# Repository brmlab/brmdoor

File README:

=== Brmdoor control software ===

brmd/ - integration hub that collects data from various sources and provides
unified reporting on IRC and web etc.
install dependecies:
  aptitude install git libimage-magick-perl liblogger-syslog-perl libdevice-serialport-perl\
    libpoe-perl libtie-ixhash-perl screen libpoe-component-server-http-perl libexpat1-dev\
    libxml-simple-perl libpoe-component-irc-perl arduino-mk
  cpan> install WWW::WolframAlpha

brmdoor/ - Arduino software

Project webpage: http://brmlab.cz/project/brmdoor

Note for PN532 version: if you want brmdoor to add card UID after "CARD"
message (not just nick), set printFullUID to true in brmdoor/brmdoor.ino.

==== Adding new UIDs to the database ====

There are two lists - the new proper and the old deperecated with truncated UIDs.
When adding, the new list is better place.

The new proper list is searched for UIDs first.

===== Using the new proper list - recommended =====

Edit the cardids_proper.h file and add your UID and nick to a new line, which
will become part of the ACLproper array. E.g. to add UID 04c24ce9ad2780 that is
7 bytes long and adding nick "voyeur1", add line:

  { 7, {0x04, 0xc2  0x4c, 0xe9, 0xad, 0x27, 0x80}, "voyeur1" },

===== Using the old broken truncated list - not recommended =====

Edit the cardids.h file. If the new card UID is 4 bytes long, e.g. 35b018d4,
compute BCC, which is xor of these four bytes (0x49 in this case). Then add

  { {0x00, 0x00, 0x35, 0xb0, 0x18, 0xd4, 0x49}, "mifare_classic_1" },

The first two bytes are magic bytes that originate in the old reader, just use
two zero bytes as above. The last byte is BCC we computed before. But you can
use zero, the software doesn't need it.

If the card UID is longer than 4 bytes (7 or 10 bytes), e.g. 04c24ce9ad2780,
discard last four bytes of the UID and prepend 0x88. Use this "newly" created
UID as if the card had only 4 byte UID, just like above.

  { {0x00, 0x00, 0x88, 0x04, 0xc2, 0x4c, 0x02}, "truncated_voyeur1" },

The old reader didn't support ISO14443 SELECT cascade 2 and 3. Hence the broken
UIDs.

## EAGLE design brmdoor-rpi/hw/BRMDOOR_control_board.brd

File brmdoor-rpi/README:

This is quick and dirty version of brmdoor that does not require Arduino, and runs only on Raspberry Pi.

This version of brmdoor requires:
- create user brmdoor, ~brmdoor/.screenrc
- create /etc/systemd/system/brmdoor.service in case systemd is used to autostart brmdoor service
- irssi configured according to ./irssi/config with loaded scripts from ./irssi/scripts
- libnfc-compatible smartcard reader
- libnfc installed
- create /etc/nfc/libnfc.conf using content from libnfc.conf supplied (otherwise nfc-list wouldnt find your NFC device)
- nfc-getcard.c compiled against libnfc (with -lnfc) and saved as "./nfc-getcard"
- to be running on RaspberryPi (or simillar with GPIO pins exported through /proc)
- variables in brmdoor-rpi.sh modified according to reality
- list of allowed cards in allowed.list in the correct format

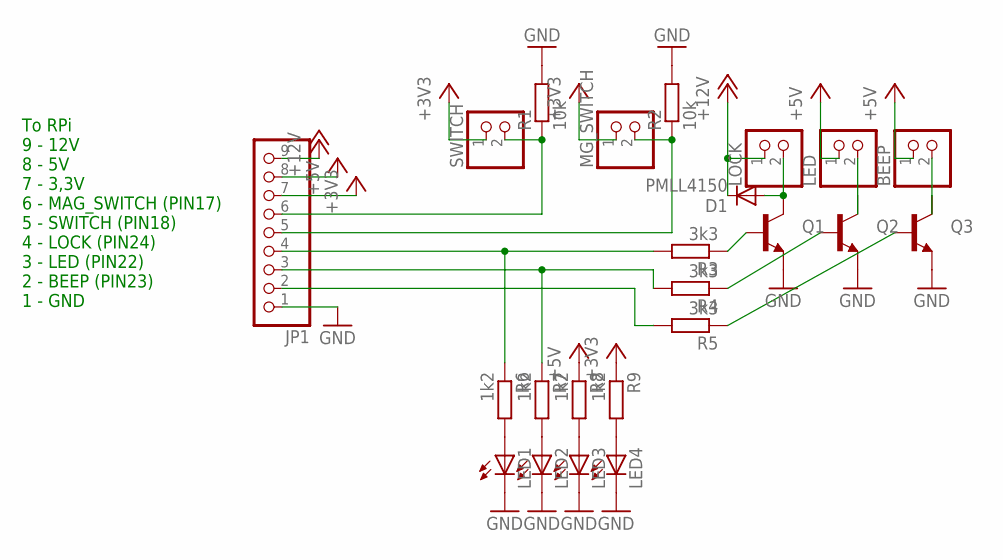
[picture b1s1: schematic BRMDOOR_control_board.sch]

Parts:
BEEP: PINHD-1X2; 1X02
D1: PMLL4150; SOD80C
JP1: PINHD-1X9; 1X09
LED: PINHD-1X2; 1X02
LED1, LED2, LED3, LED4: LEDKA-3528ASYC; KA-3528ASYC
LOCK: PINHD-1X2; 1X02
MG_SWITCH: PINHD-1X2; 1X02
Q1, Q2, Q3: TRANSISTOR_NPNSMD2; SOT223
R1, R2: 10k; M1206
R3, R4, R5: 3k3; M1206
R6, R7, R8, R9: 1k2; M1206
SWITCH: PINHD-1X2; 1X02

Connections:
+3V3: JP1.7, MG_SWITCH.1, R9.1, SWITCH.1
+5V: BEEP.1, JP1.8, LED.1, R8.1
+12V: D1.C, JP1.9, LOCK.1
GND: JP1.1, LED1.C, LED2.C, LED3.C, LED4.C, Q1.3 (E), Q2.3 (E), Q3.3 (E), R1.2, R2.2
unnamed: JP1.6, R1.1, SWITCH.2
unnamed: JP1.5, MG_SWITCH.2, R2.1
unnamed: Q1.1 (B), R3.1
unnamed: Q2.1 (B), R4.1
unnamed: Q3.1 (B), R5.1
unnamed: JP1.4, R3.2, R6.1
unnamed: JP1.3, R4.2, R7.1
unnamed: JP1.2, R5.2
unnamed: LED1.A, R6.2
unnamed: LED2.A, R7.2
unnamed: LED3.A, R8.2
unnamed: LED4.A, R9.2
unnamed: D1.A, LOCK.2, Q1.2 (C)
unnamed: LED.2, Q2.2 (C)
unnamed: BEEP.2, Q3.2 (C)

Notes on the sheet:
To RPi 9 - 12V 8 - 5V 7 - 3,3V 6 - MAG_SWITCH (PIN17) 5 - SWITCH (PIN18) 4 - LOCK (PIN24) 3 - LED (PIN22) 2 - BEEP (PIN23) 1 - GND

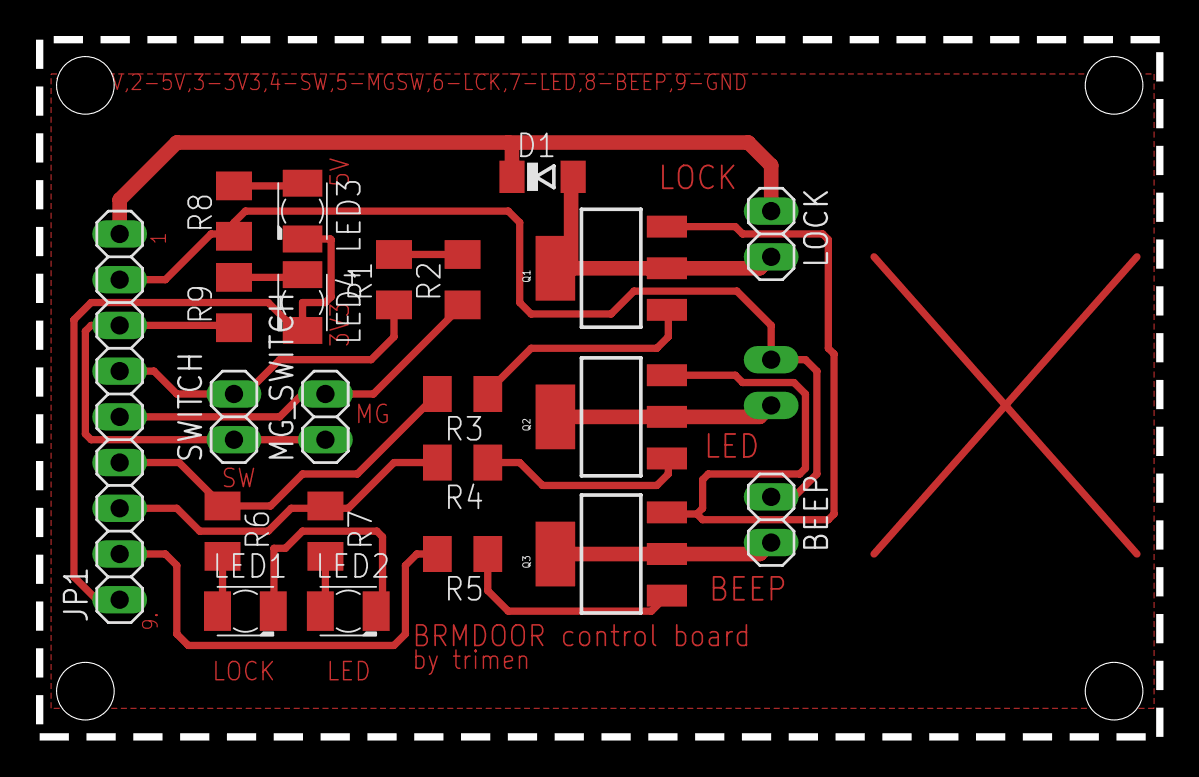
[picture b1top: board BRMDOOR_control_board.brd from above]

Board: 2 copper layers, 62.2 x 38.7 mm, 23 parts (1 on the bottom side), 19 nets.

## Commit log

2010-11-08 init
2010-11-12 started to work on C rewrite to deploy directly on WRT
2010-12-09 add WIP python version
2011-03-09 Remove unfinished experiments
2011-03-09 Replace brmdoor.php by full-fledged universal hub script brmd
    brmd should handle various kinds of brmlab-related events (brmdoor
    unlocks, status panel events, wiki updates) and provide central place
    to handle them, with unified interface (web and IRC).
    Currently, all of this should be implemented, except wiki updates
    handling. But the script is still a bit rudimentary; some TODO items
    are mentioned in the TODO file.
2011-03-09 brmstatus.txt interface support
2011-03-09 brmd.pl: Fix permissions
2011-03-09 brmstatus.txt: Add link to front page
2011-03-09 Web /brmd/: Add link to view source
2011-03-09 add arduino sketch
2011-03-09 add pitches.h
2011-03-09 use macro for music
2011-03-11 brmd: Try to deal with IRC disconnects gracefully
2011-03-11 brmdoor: Add timestamps to log, log each brmdoor input for now
2011-03-11 brmd IRC: Sync topic with internal state on connect
2011-03-13 Move files to directories brmd/, sketch/
2011-03-13 sketch: Convert from ethernet shield to USB serial comunication
    Ethernet shield has been extremely unreliable, and we need a USB host nearby for a webcam anyway.
2011-03-14 brmd: Brmdoor is no longer TCP service but local serial
2011-03-16 small fixes, add NewSoftSerial lib
2011-04-26 sketch: Support for status overrides from host over comSerial
2011-04-26 brmd: Update icons
2011-04-26 brmd: Force HTTP/1.1 replies
    It seems to reduce the fd leaks by an order of magnitude.
2011-04-26 brmd: Factor out status_update(), record_update()
2011-04-26 brmd: Support for manual status override using web button
2011-05-01 brmd.pl web_brmstatus_html: Change input button to submit
2011-05-01 brmd: Allow device filename override on commandline
2011-05-01 remove confusing sentence
2011-05-01 add readme
2011-05-03 print also url of videostream
2011-05-03 brmd: Show stream URL only on IRC
2011-05-03 brmd: Switch streaming on brmvid when record switch is pressed
2011-05-03 brmd: Show brmstream link on main web page when on air
2011-05-03 brmd: Update stream status in topic too
2011-05-03 brmd: Factor out stream URL to $streamurl
2011-05-03 brmd record_update(): Call topic_update()
2011-05-04 fix show source link
2011-05-06 brmd: Separate IRC interface to the brmd::IRC package
2011-05-06 brmd: Separate WWW interface to the brmd::WWW package
2011-05-06 brmd: Separate serial interface to the brmd::Door package
2011-05-06 brmd::WWW: Move use HTTP::Status, CGI there
2011-05-06 brmd::IRC: Replace topic_update, notify with more specific events
2011-05-06 brmd: Separate ssh interface to the brmd::Stream package
2011-05-07 brmd status_update, record_update: Transform to events, introduce event registration
2011-05-07 brmd: Move manual update logic from web_brmstatus_switch() to status_update()
2011-05-07 brmd::Door: Introduce event status_override
2011-05-07 brmd::WWW notify_update(): Merge in notify_manual_update()
2011-05-07 brmd: $record -> $streaming
2011-05-07 brmd streaming_update(): Remove superfluous line
2011-05-08 Added AlphaSign notification of streaming status
2011-05-10 brmd: Copyright notice
2011-05-10 brmd: Separate Alphasign interface to the brmd::Alphasign package
2011-05-12 brmd: $device -> $devdoor
2011-05-12 brmd::Door::register(): Fix observer refcount id
2011-05-12 TODO: Remove implemented features
2011-05-12 brmd::Alphasign: Manage serial directly, no external helper
2011-05-17 brmd: Update default device names to use by-id paths
2011-05-17 brmd: Fix taking $devasign from commandline
2011-05-17 brmd: Full support for alphasign, including all markup and web interface
2011-05-18 brmd::Alphasign: Improved input checking
2011-05-18 brmd::Alphasign: Remember last mode too
2011-05-18 brmd::Alphasign: Beep on stream_start()
2011-05-18 brmd::Alphasign: Add beep checkbox to web interface
2011-05-19 fix roll_up
2011-06-02 brmd: Update streamurl to Jenda's restreaming server
2011-06-22 add wolfram alpha (!alpha) command
2011-06-22 fix concatenation
2011-06-22 rework answer
2011-06-22 add nick
2011-06-22 use - instead of :
2011-06-22 sanitise newlines
2011-07-05 allow change of alphasign even while streaming
2011-07-05 Revert "allow change of alphasign even while streaming"
    This reverts commit adaaad8084e3b1f4ad81c1f069aa11c8cbd61aa1.
2011-07-31 fix output
2011-08-29 Enhanced WolframAlpha output display, limit number of lines
2011-08-30 brmd: Convert modes,markup from our to my, local to Alphasign
2011-08-30 Sketch: Fix reading new video/status state
2011-08-30 Fix manual status change desyncing arduino
2011-09-07 stream URL simplification
2011-09-08 few lines to README
2011-10-18 Sketch: Fix card number output
2011-10-18 Sketch: Fix override over serial
2011-10-18 brmd notify_door_unauth: Include cardid parameter
2011-10-18 brmd notify_door_*: Route through the main session
2011-10-18 brmd notify_door_unauth IRC: Bold message
2011-10-18 brmd::Log: New POE component, logging notify_door_* using Logger::Syslog
2011-10-18 IRC notify_door_unlocked: Do not log nickname due to popular demand
2011-10-18 Track dooropen ajar/shut state using a magnetic sensor, log verbosely for now
2011-10-18 Sketch: Reduce unnecessary delay after card event
2011-10-18 Sketch: Support an 'a' command to play alarm sound
2011-10-18 brmd notify_door_open: Move alert logic from IRC to main session
2011-10-18 brmd Door play_alarm: New method
2011-10-18 brmd alert: Do not trigger on door open just after brmlab closed
2011-10-19 brmd stream_switch: Use ssh username brmlab inst. of brmstream
2011-10-20 brmd::Log notify_door_open: Add logging routine
2011-10-20 brmd::IRC notify_door_open: Report only alert conditions
2011-10-20 brmd alert condition: Consider dangerous opens also in case of status manual override active
2012-02-10 brmd.pl: stopbits 2 now needed for whatever reason
2012-06-09 brmd.pl: Fix multi-channel support
2013-01-08 brmd.pl: Use HTTP/1.0 inst. of HTTP/1.1 to avoid pipelining problems (unclosed connections)
2013-01-08 brmd.pl: Disable alphasign communication in a super-dirty way
2013-01-08 brmd.pl: Add support for the SpaceAPI json output; code provided by ruza
2013-01-12 fix irc position in spaceapi json
2013-01-12 use better logo
2013-01-14 add facebook to spaceapi json
2013-02-28 spaceapi 0.13 changes prepared for future use
    validated in OpenSpaceLint validator http://openspace.slopjong.de/
    beware, can possibly break compatibility with applications with
    spaceapi 0.12 and older because "status" is string in spaceapi
    versions up to 0.12 and object in spaceapi 0.13
    http://openspace.slopjong.de/specs/0.13
    http://openspace.slopjong.de/specs/changelog
2013-05-02 end logo with .png
2013-05-02 change geocoordinates
2013-05-30 JSON formalize
2013-06-10 status -> state, cache-control
    JSON compliant to the specs 0.13, 0.12, 0.11, 0.9, 0.8 spaceapi
2013-06-11 contact.foursquare added
2013-06-17 README.raspberry added
2013-06-18 debian startup script
2013-06-18 brmdoor: Convert from NewSoftSerial to SoftwareSerial
2013-06-18 brmdoor.pde -> brmdoor.ino
2013-06-18 Makefile: arduino-mk thingie
2013-06-27 Make it working with latest Arduino
2013-06-27 Make it working, part 2
2013-08-25 write text "Since <date, time>" to generated icon
2014-03-25 Added Adafruit PN532 library
2014-03-25 Added gitignore
2014-03-25 Rewritten to use PN532 reader over SPI
2014-03-25 Note about printFullUID variable
2014-03-25 Printing UIDs enabled by default in CARD message
2014-03-25 Added PN532 library to Makefile libs
2014-03-25 Formatting hex numbers
2014-03-25 Changed default board ID since the board was physically changed
2014-03-26 Gitignore for header with proper UID cards that should not be public
2014-03-26 Implemented proper ACL with full UIDs
2014-03-26 Created new ACL list that can store full card UIDs up to 10 bytes (max UID length by NXP specs).
2014-03-26 Howto for adding new card numbers in README
2014-03-26 Added sample card array definitions
2014-06-14 Implementation of brmdoor downstairs
2014-06-14 brmdoor-rpi: Tone down IRC messages, better consistency with brmd
2014-06-27 Adjusted beeping, logging is now async
2014-06-27 Don't flood NFC errors
2014-08-05 Melody played when access denied by Jenda.
2014-12-02 ARDUINO_PORT change
2014-12-23 status icon load balanced via DNS
    status.brmlab.cz
2014-12-23 debian.init stop and restart
2015-01-13 Alarm timeout increased
2016-04-21 Added files via upload
2016-06-07 Update README
    updated dependencies for brmd.pl at debian
2017-04-22 Configuration is no longer hardcoded, spaceapi support implemented
2017-05-03 Allow dot in card owner name
2017-06-01 push-cardids.sh update

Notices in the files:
parts and their libraries:
SparkFun-DiscreteSemi: Licensing: Creative Commons ShareAlike 4.0 International - https://creativecommons.org/licenses/by-sa/4.0
